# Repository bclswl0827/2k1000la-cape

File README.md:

# 2K1000LA Monitor + 3-Port USB 2.0 Hub Cape

The LCD1602 monitor + 3-Port USB 2.0 Hub cape for Loongson 2K1000LA Development Board. Used to display the system IP address and expand the USB interface.

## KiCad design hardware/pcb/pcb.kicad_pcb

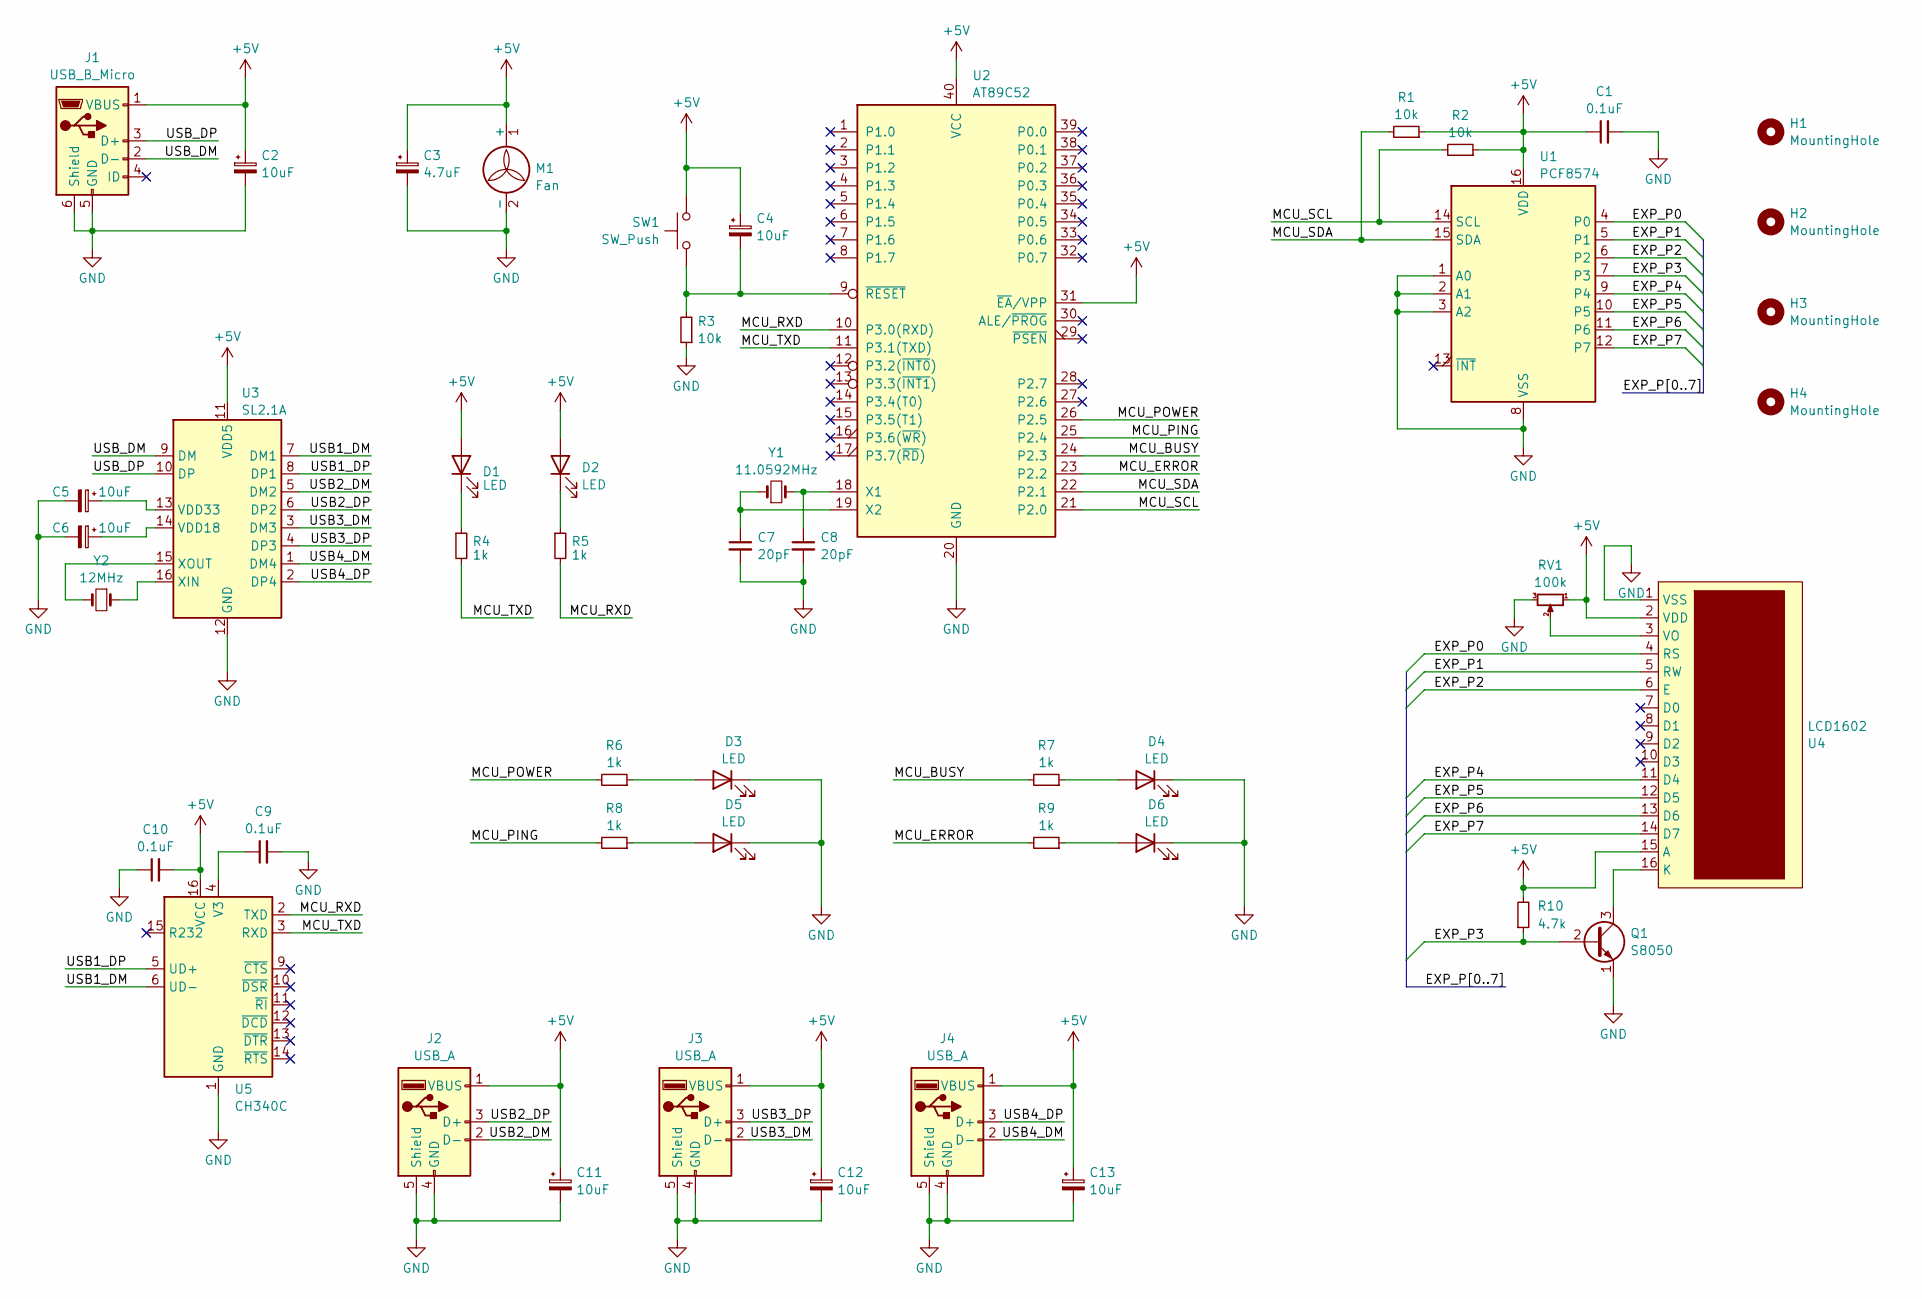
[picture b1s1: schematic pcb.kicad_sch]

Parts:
C1, C9, C10: 0.1uF; C_Disc_D3.0mm_W2.0mm_P2.50mm
C2, C4, C5, C6, C11, C12, C13: 10uF; CP_Radial_D5.0mm_P2.50mm
C3: 4.7uF; CP_Radial_D5.0mm_P2.50mm
C7, C8: 20pF; C_Disc_D3.0mm_W2.0mm_P2.50mm
D1, D2, D3, D4, D5, D6: LED; LED_D3.0mm
H1, H2, H3, H4: MountingHole; MountingHole_3.2mm_M3
J1: USB_B_Micro; USB_Micro-B_Molex-105017-0001
J2, J3, J4: USB_A; USB_A_CONNFLY_DS1095-WNR0
M1: Fan; Fan_30x30mm
Q1: S8050; TO-92_Inline
R1, R2, R3: 10k; R_Axial_DIN0204_L3.6mm_D1.6mm_P7.62mm_Horizontal
R4, R5, R6, R7, R8, R9: 1k; R_Axial_DIN0204_L3.6mm_D1.6mm_P7.62mm_Horizontal
R10: 4.7k; R_Axial_DIN0204_L3.6mm_D1.6mm_P7.62mm_Horizontal
RV1: 100k; Potentiometer_Bourns_3296W_Vertical
SW1: SW_Push; SW_SPST_FSMSM
U1: PCF8574; SOIC-16W_7.5x10.3mm_P1.27mm
U2: AT89C52; DIP-40_W15.24mm
U3: SL2.1A; SOIC-16_3.9x9.9mm_P1.27mm
U4: LCD1602; PinSocket_1x16_P2.54mm_Vertical
U5: CH340C; SOIC-16_3.9x9.9mm_P1.27mm
Y1: 11.0592MHz; Crystal_HC18-U_Vertical
Y2: 12MHz; Crystal_HC18-U_Vertical

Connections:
+5V: C1.1, C2.1, C3.1, C4.1, C10.2, C11.1, C12.1, C13.1, D1.2 (A), D2.2 (A), J1.1 (VBUS), J2.1 (VBUS), J3.1 (VBUS), J4.1 (VBUS), M1.1 (+), R1.1, R2.1, R10.2, RV1.1, SW1.1, U1.16 (VDD), U2.31 (~EA/VPP), U2.40 (VCC), U3.11 (VDD5), U4.2 (VDD), U4.15 (A), U5.16 (VCC)
/EXP_P0: U1.4 (P0), U4.4 (RS)
/EXP_P1: U1.5 (P1), U4.5 (RW)
/EXP_P2: U1.6 (P2), U4.6 (E)
/EXP_P3: Q1.2 (B), R10.1, U1.7 (P3)
/EXP_P4: U1.9 (P4), U4.11 (D4)
/EXP_P5: U1.10 (P5), U4.12 (D5)
/EXP_P6: U1.11 (P6), U4.13 (D6)
/EXP_P7: U1.12 (P7), U4.14 (D7)
/MCU_BUSY: R7.2, U2.24 (P2.3)
/MCU_ERROR: R9.2, U2.23 (P2.2)
/MCU_PING: R8.2, U2.25 (P2.4)
/MCU_POWER: R6.2, U2.26 (P2.5)
/MCU_RXD: R5.2, U2.10 (P3.0(RXD)), U5.2 (TXD)
/MCU_SCL: R2.2, U1.14 (SCL), U2.21 (P2.0)
/MCU_SDA: R1.2, U1.15 (SDA), U2.22 (P2.1)
/MCU_TXD: R4.2, U2.11 (P3.1(TXD)), U5.3 (RXD)
/USB1_DM: U3.7 (DM1), U5.6 (UD-)
/USB1_DP: U3.8 (DP1), U5.5 (UD+)
/USB2_DM: J2.2 (D-), U3.5 (DM2)
/USB2_DP: J2.3 (D+), U3.6 (DP2)
/USB3_DM: J3.2 (D-), U3.3 (DM3)
/USB3_DP: J3.3 (D+), U3.4 (DP3)
/USB4_DM: J4.2 (D-), U3.1 (DM4)
/USB4_DP: J4.3 (D+), U3.2 (DP4)
/USB_DM: J1.2 (D-), U3.9 (DM)
/USB_DP: J1.3 (D+), U3.10 (DP)
GND: C1.2, C2.2, C3.2, C5.2, C6.2, C7.2, C8.2, C9.2, C10.1, C11.2, C12.2, C13.2, D3.1 (K), D4.1 (K), D5.1 (K), D6.1 (K), J1.5 (GND), J1.6 (Shield), J2.4 (GND), J2.5 (Shield), J3.4 (GND), J3.5 (Shield), J4.4 (GND), J4.5 (Shield), M1.2 (-), Q1.1 (E), R3.1, RV1.3, U1.1 (A0), U1.2 (A1), U1.3 (A2), U1.8 (VSS), U2.20 (GND), U3.12 (GND), U4.1 (VSS), U5.1 (GND)
unnamed: D1.1 (K), R4.1
unnamed: D2.1 (K), R5.1
unnamed: D3.2 (A), R6.1
unnamed: D4.2 (A), R7.1
unnamed: D5.2 (A), R8.1
unnamed: D6.2 (A), R9.1
unnamed: Q1.3 (C), U4.16 (K)
unnamed: C8.1, U2.18 (X1), Y1.2
unnamed: C7.1, U2.19 (X2), Y1.1
unnamed: C4.2, R3.2, SW1.2, U2.9 (~RESET)
unnamed: C6.1, U3.14 (VDD18)
unnamed: C5.1, U3.13 (VDD33)
unnamed: U3.16 (XIN), Y2.1
unnamed: U3.15 (XOUT), Y2.2
unnamed: RV1.2, U4.3 (VO)
unnamed: C9.1, U5.4 (V3)

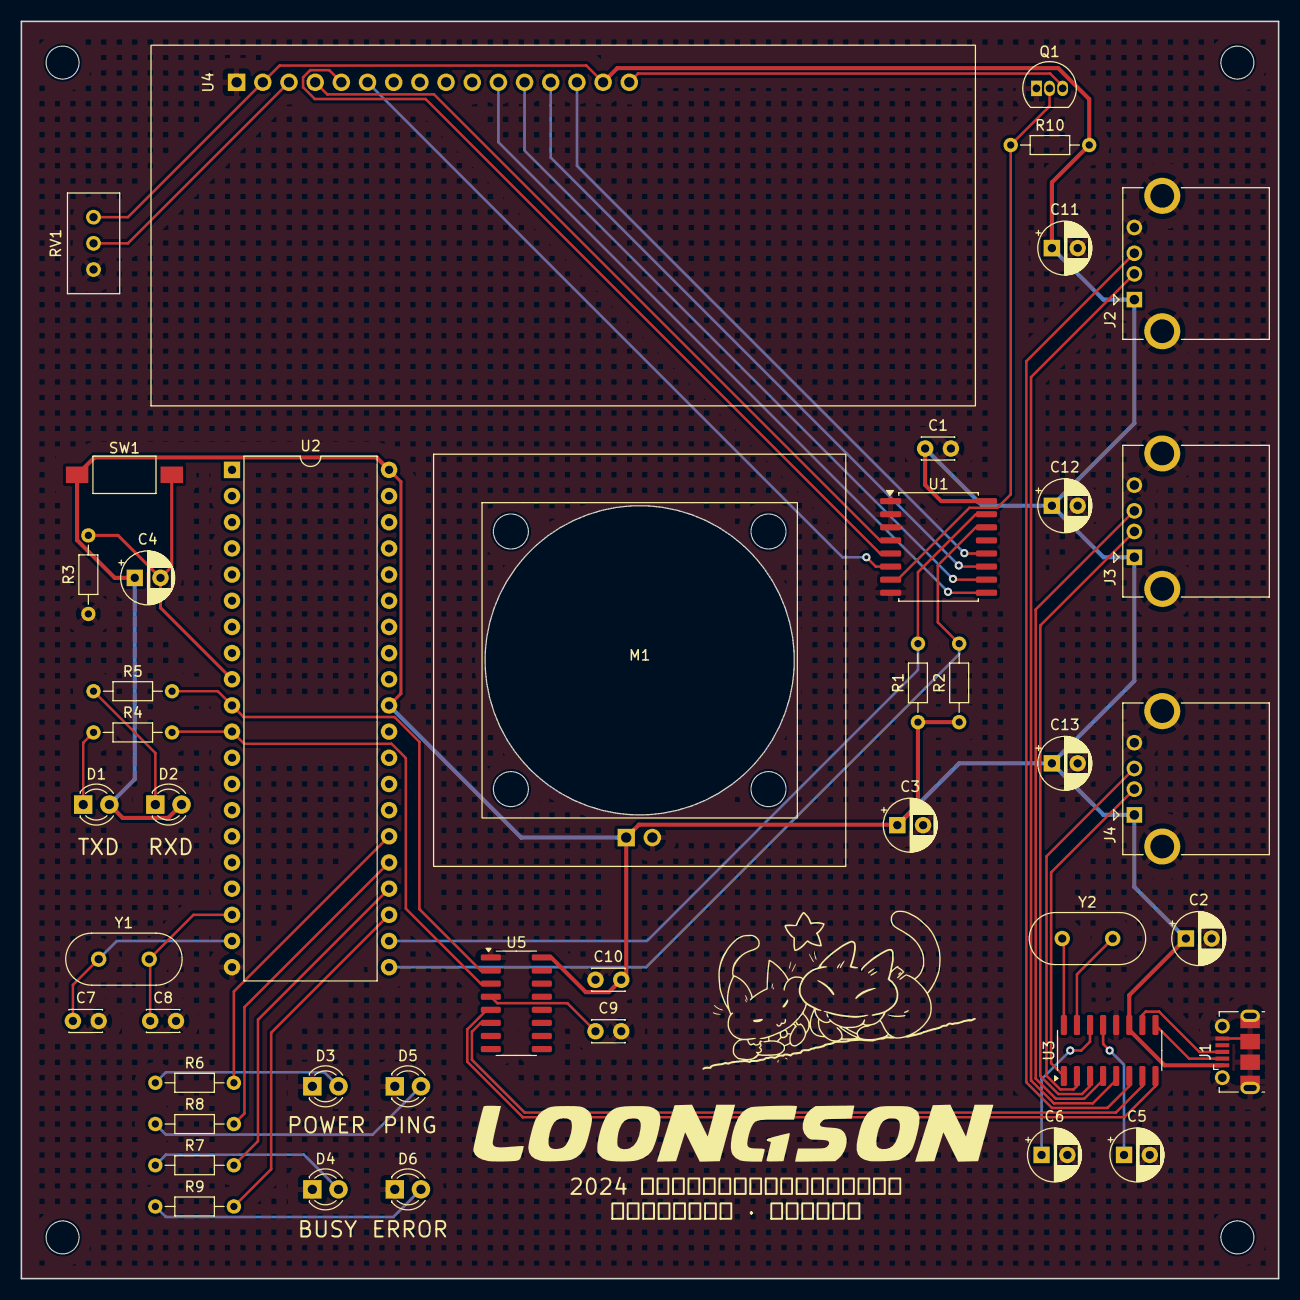
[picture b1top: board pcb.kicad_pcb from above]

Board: 2 copper layers, 122.0 x 122.0 mm, 48 parts (0 on the bottom side), 44 nets.

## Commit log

2024-06-12 Upload source files
2024-06-12 Change package name
2024-06-12 Add systemd service file
2024-06-12 Catch more system signals
2024-06-12 Skip interface with no IP address
2024-06-12 always get interface name
2024-06-17 Print timeout message when no data received
2024-06-17 Adjust timer
2024-06-19 Set longer detection interval
2024-06-19 Set firmware timeout threshold to 60 seconds
2024-12-22 chore: Update startup message
